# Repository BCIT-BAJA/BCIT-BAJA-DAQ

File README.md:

# Problem 
During the last BAJA competition,The BAJA team was unable to measure dynamic forces applied onto the suspension of the car. As a result, during the last competition, it bent.

The telemetry system for BCIT-BAJA car, collects strain across suspension components of car to allow BAJA to optimize material and reinforce weak areas of suspension.
As well as collect other data such as linear/angular acceleration.

There consists of 2 parts of this project. 

**PART B** the amplification of the (-15-15mV) analog strain signal to (0-3.0V) which is then routed to

**PART A**, which collects the 8 conditioned analog signals and is transmitted/received over a 915MHz antenna

# MAINBOARD( PART A)

Power supply circuitry

Conditioning of analog signals 

Additional peripherals used

# Amplifier circuit ( PART B) - 

Example of LTSPICE simulation used for amplifier board + signal conditioning

Verified amplifier board working

# Results of real-world appied force vs output voltage

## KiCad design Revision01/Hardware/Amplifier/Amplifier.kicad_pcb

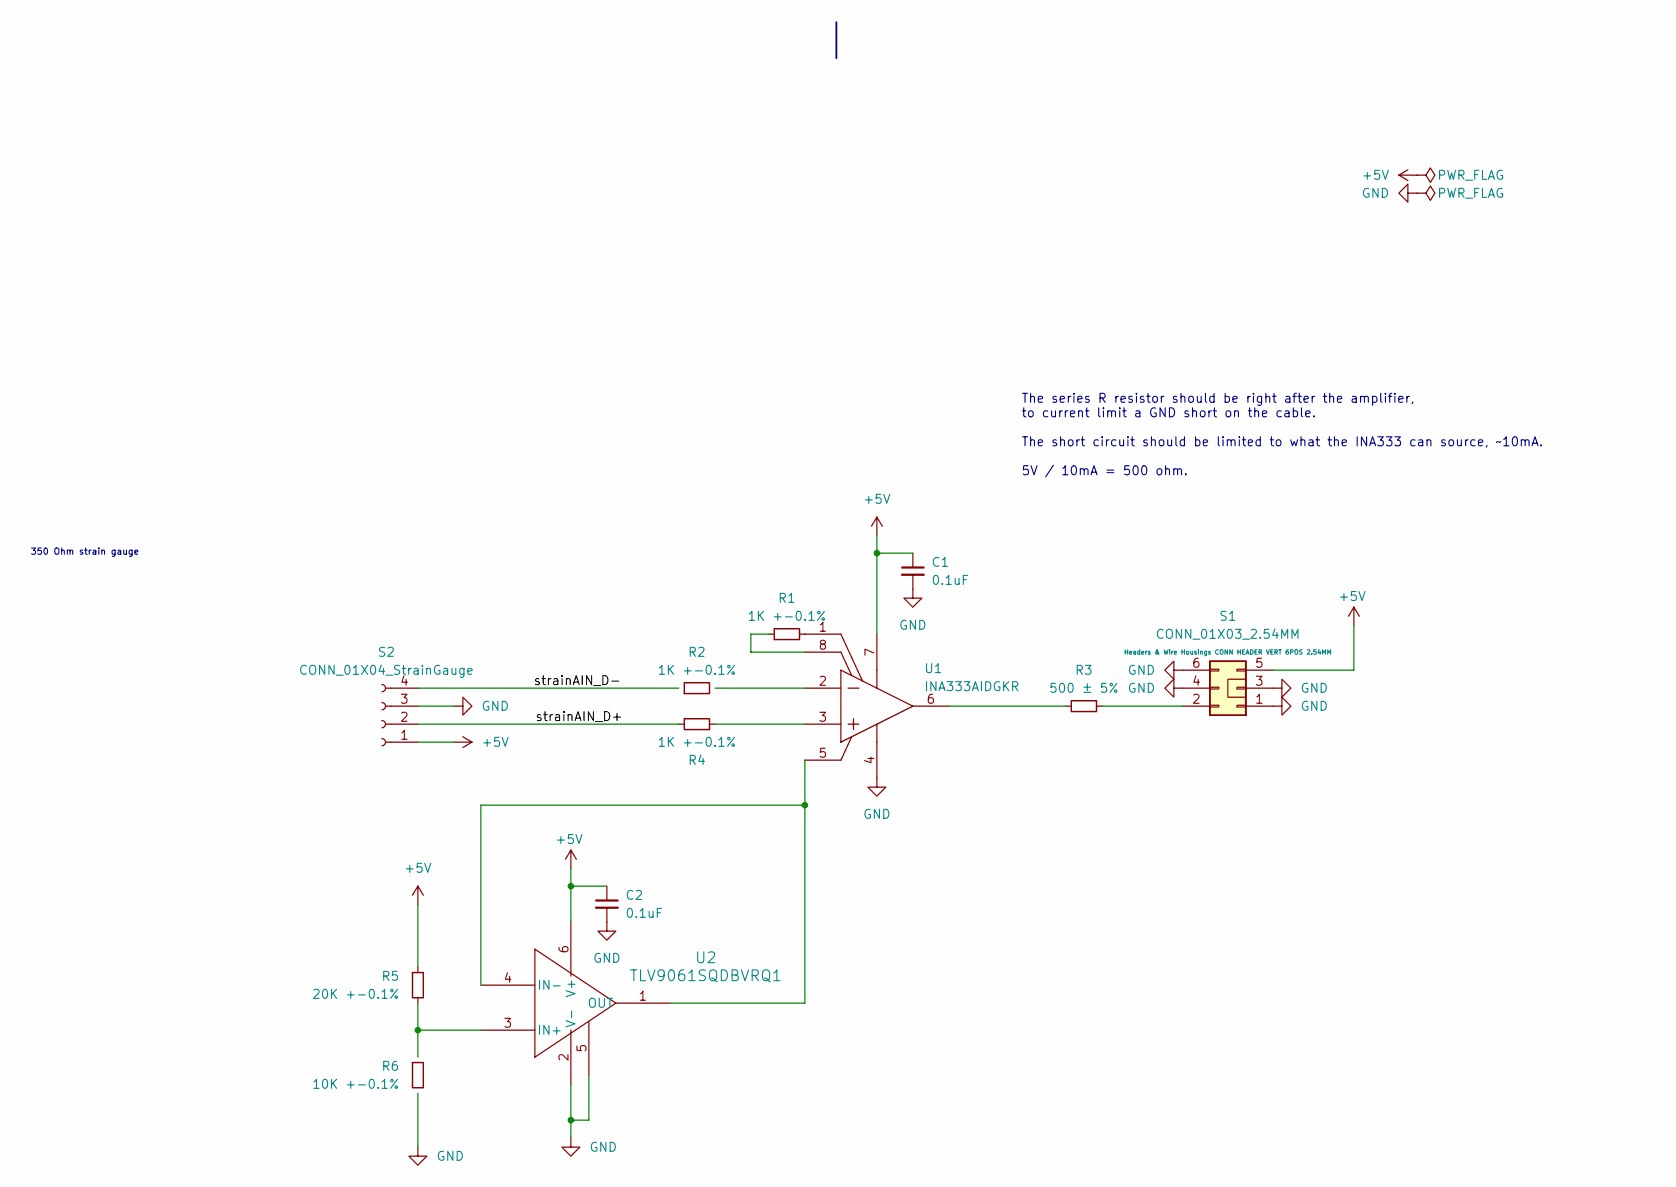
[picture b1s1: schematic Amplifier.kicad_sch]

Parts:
C1, C2: 0.1uF; C_0805_2012Metric_Pad1.18x1.45mm_HandSolder; Manufacturer Part Number CL21B104KBCNNWC; Mouser Part Number 187-CL21B104KBCNNWC
R1, R2, R4: 1K +-0.1%; R_0805_2012Metric_Pad1.20x1.40mm_HandSolder; Manufacturer Part Number MCU08050D1001BP500; Mouser Part Number 594-MCU0805D1001BP5
R3: 500 ± 5%; R_0805_2012Metric_Pad1.20x1.40mm_HandSolder; Manufacturer Part Number MCU0805MD4990DP500; Mouser Part Number 594-MCU0805MD4990DP5
R5: 20K +-0.1%; R_0805_2012Metric_Pad1.20x1.40mm_HandSolder; Manufacturer Part Number RG2012P-203-B-T5; Mouser Part Number 754-RG2012P-203-B-T5
R6: 10K +-0.1%; R_0805_2012Metric_Pad1.20x1.40mm_HandSolder; Manufacturer Part Number RG2012P-103-B-T5; Mouser Part Number 754-RG2012P-103-B-T5
S1: CONN_01X03_2.54MM; AdamTech_BHR-06-VUA; Manufacturer Part Number BHR-06-VUA; Mouser Part Number 737-BHR-06-VUA
S2: CONN_01X04_StrainGauge; CONN_01X04
U1: INA333AIDGKR; INA333AIDGKR_SOP65P490X110-8N; Manufacturer Part Number INA333AIDGKR; Mouser Part Number 595-INA333AIDGKR
U2: TLV9061SQDBVRQ1; TSOT-23-6; Manufacturer Part Number TLV9061SQDBVRQ1; Mouser Part Number 595-TLV9061SQDBVRQ1

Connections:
+5V: C1.1, C2.1, R5.1, S1.5, S2.1, U1.7 (V+), U2.6 (V+)
/strainAIN_D+: R4.2, S2.2
/strainAIN_D-: R2.1, S2.4
GND: C1.2, C2.2, R6.2, S1.1, S1.3, S1.4, S1.6, S2.3, U1.4 (V-), U2.2 (V-), U2.5
unnamed: R1.1, U1.8 (RG)
unnamed: R1.2, U1.1 (RG)
unnamed: R3.1, S1.2
unnamed: U1.5 (REF), U2.1 (OUT), U2.4 (IN-)
unnamed: R4.1, U1.3 (VIN+)
unnamed: R2.2, U1.2 (VIN-)
unnamed: R3.2, U1.6 (VOUT)
unnamed: R5.2, R6.1, U2.3 (IN+)

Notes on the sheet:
350 Ohm strain gauge
The series R resistor should be right after the amplifier, to current limit a GND short on the cable. The short circuit should be limited to what the INA333 can source, ~10mA. 5V / 10mA = 500 ohm.

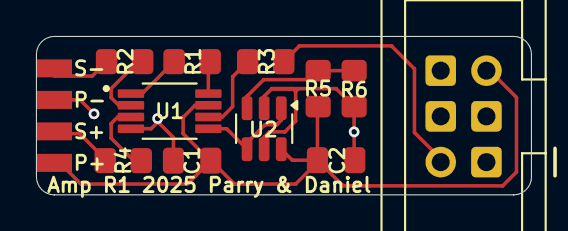
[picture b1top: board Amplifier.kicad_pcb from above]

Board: 2 copper layers, 27.5 x 8.8 mm, 12 parts (0 on the bottom side), 12 nets.

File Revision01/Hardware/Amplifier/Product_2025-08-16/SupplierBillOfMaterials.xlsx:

# | Reference | Quantity | Qty | Qty Multiplier | Value | Description | Package | Footprint | Detailed Description | Datasheet | Manufacturer | Manufacturer Part Number | Mouser Link | Mouser Part Number | Exclude from BOM | DNP | Exclude from Board
1 | C1,C2 | 2 | 2 |  | 0.1uF | Multilayer Ceramic Capacitors MLCC - SMD/SMT 100nF+/-10% 50V X7R 0805 | 0805 (2012 Metric) | Capacitor_SMD:C_0805_2012Metric_Pad1.18x1.45mm_HandSolder |  | https://www.mouser.ca/datasheet/2/585/MLCC-1837944.pdf | Samsung Electro-Mechanics | CL21B104KBCNNWC | https://www.mouser.ca/ProductDetail/Samsung-Electro-Mechanic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 | 187-CL21B104KBCNNWC
2 | R1,R2,R4 | 3 | 3 |  | 1K +-0.1% | Thin Film Resistors - SMD .05W 1Kohms 0.1% 0805 25ppm | 0805 (2012 Metric) | Resistor_SMD:R_0805_2012Metric_Pad1.20x1.40mm_HandSolder |  | https://www.vishay.com/doc?28700 | Vishay / Beyschlag | MCU08050D1001BP500 | https://www.mouser.ca/ProductDetail/Vishay-Beyschlag/MCU0805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 | 594-MCU0805D1001BP5
3 | R3 | 1 | 1 |  | 500 ± 5% | Thin Film Resistors - SMD .2W 499ohms .5% 0805 25ppm Auto | 0805 (2012 Metric) | Resistor_SMD:R_0805_2012Metric_Pad1.20x1.40mm_HandSolder |  | https://www.vishay.com/doc?28952 | Vishay / Beyschlag | MCU0805MD4990DP500 | https://www.mouser.ca/ProductDetail/Vishay-Beyschlag/MCU0805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 | 594-MCU0805MD4990DP5
4 | R5 | 1 | 1 |  | 20K +-0.1% | Thin Film Resistors - SMD 1/8W 20K Ohms 0.1% 0805 25ppm | 0805 (2012 Metric) | Resistor_SMD:R_0805_2012Metric_Pad1.20x1.40mm_HandSolder |  | https://www.mouser.ca/datasheet/2/392/n_catalog_partition01_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 | Susumu | RG2012P-203-B-T5 | https://www.mouser.ca/ProductDetail/Susumu/RG2012P-203-B-T5?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 | 754-RG2012P-203-B-T5
5 | R6 | 1 | 1 |  | 10K +-0.1% | Thin Film Resistors - SMD 1/8W 10K Ohms 0.1% 0805 25ppm | 0805 (2012 Metric) | Resistor_SMD:R_0805_2012Metric_Pad1.20x1.40mm_HandSolder |  | https://www.mouser.ca/datasheet/2/392/n_catalog_partition01_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 | Susumu | RG2012P-103-B-T5 | https://www.mouser.ca/ProductDetail/Susumu/RG2012P-103-B-T5?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 | 754-RG2012P-103-B-T5
6 | U2 | 1 | 1 |  | TLV9061SQDBVRQ1 | Operational Amplifiers - Op Amps Automotive single 5.5-V 10-MHz rail-to | SOT-23-6 | Package_TO_SOT_SMD:TSOT-23-6 |  | https://www.ti.com/lit/gpn/tlv9064-q1 | Texas Instruments | TLV9061SQDBVRQ1 | https://www.mouser.ca/ProductDetail/Texas-Instruments/TLV906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 | 595-TLV9061SQDBVRQ1
7 | U1 | 1 | 1 |  | INA333AIDGKR | Instrumentation Amplifiers Lo Pwr Prec Inst Amp A 595-INA333AIDGKT | VSSOP-8 | Lib:INA333AIDGKR_SOP65P490X110-8N |  | https://www.ti.com/lit/gpn/ina333 | Texas Instruments | INA333AIDGKR | https://www.mouser.ca/ProductDetail/Texas-Instruments/INA333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 | 595-INA333AIDGKR
35 | U4 | 2 | 1 | 2 | Adafruit 3070 | RFM69HCW TRANSCEIVER RADIO BREAK | Module | Lib:Adafruit3070 | RFM69HCW - Transceiver 868MHz, 915MHz Evaluation Board | https://cdn-learn.adafruit.com/downloads/pdf/adafruit-rfm69h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 | Adafruit Industries LLC | 3070 | https://www.mouser.ca/ProductDetail/Adafruit/3070?qs=AGnqjqv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 | 485-3070 | https://www.digikey.ca/en/products/detail/adafruit-industrie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 | 1528-1665-ND
 |  |  |  | NOTE: The Adafruit is unavailable on digikey at this time, so it is bundled wit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

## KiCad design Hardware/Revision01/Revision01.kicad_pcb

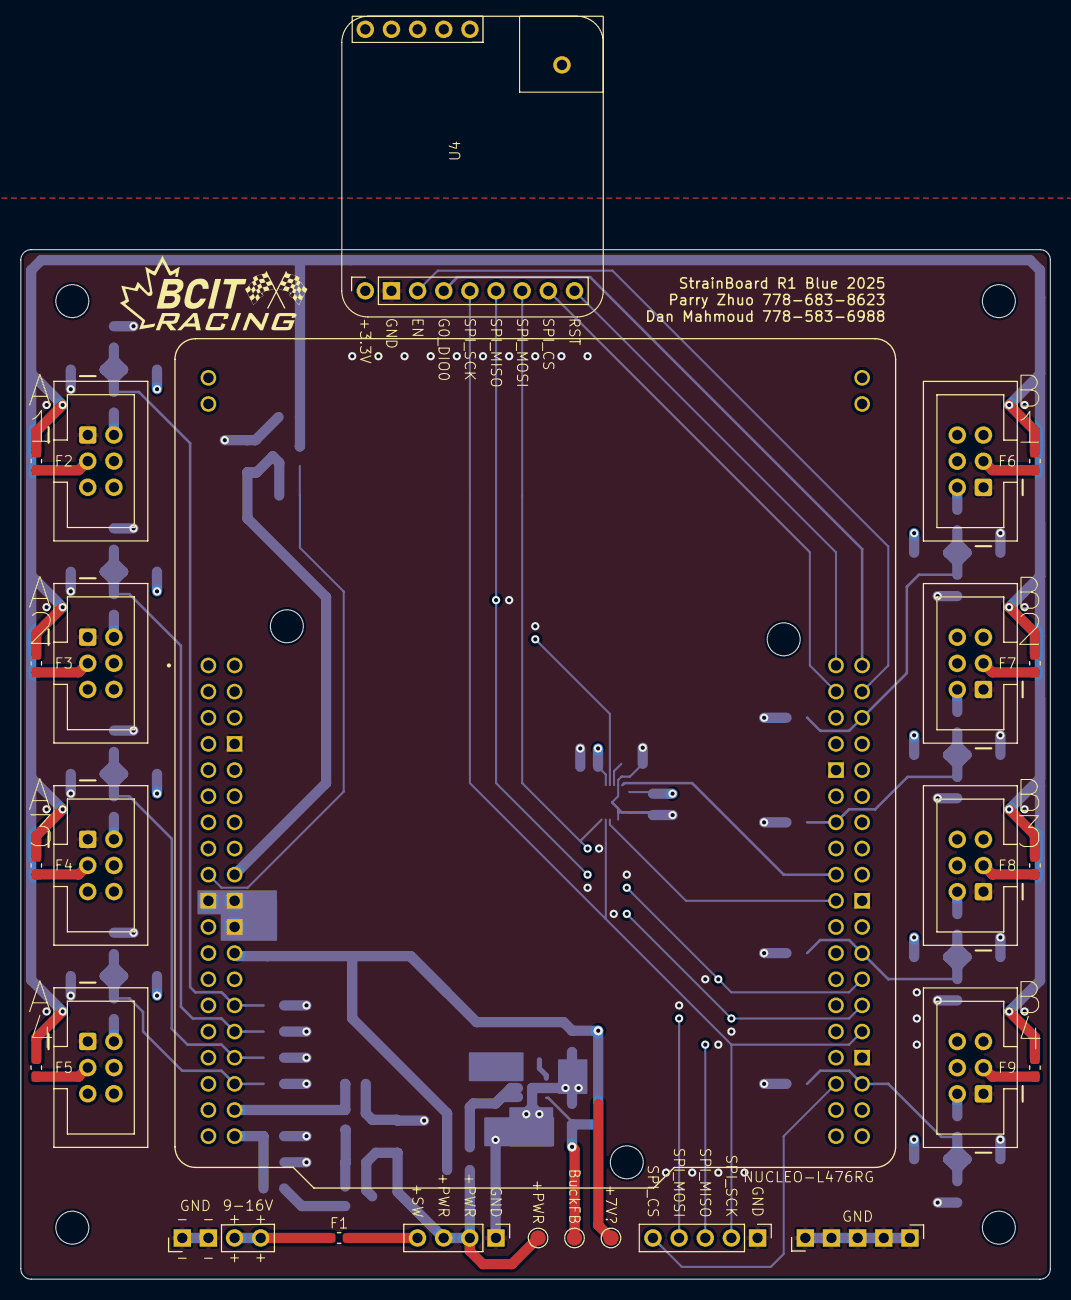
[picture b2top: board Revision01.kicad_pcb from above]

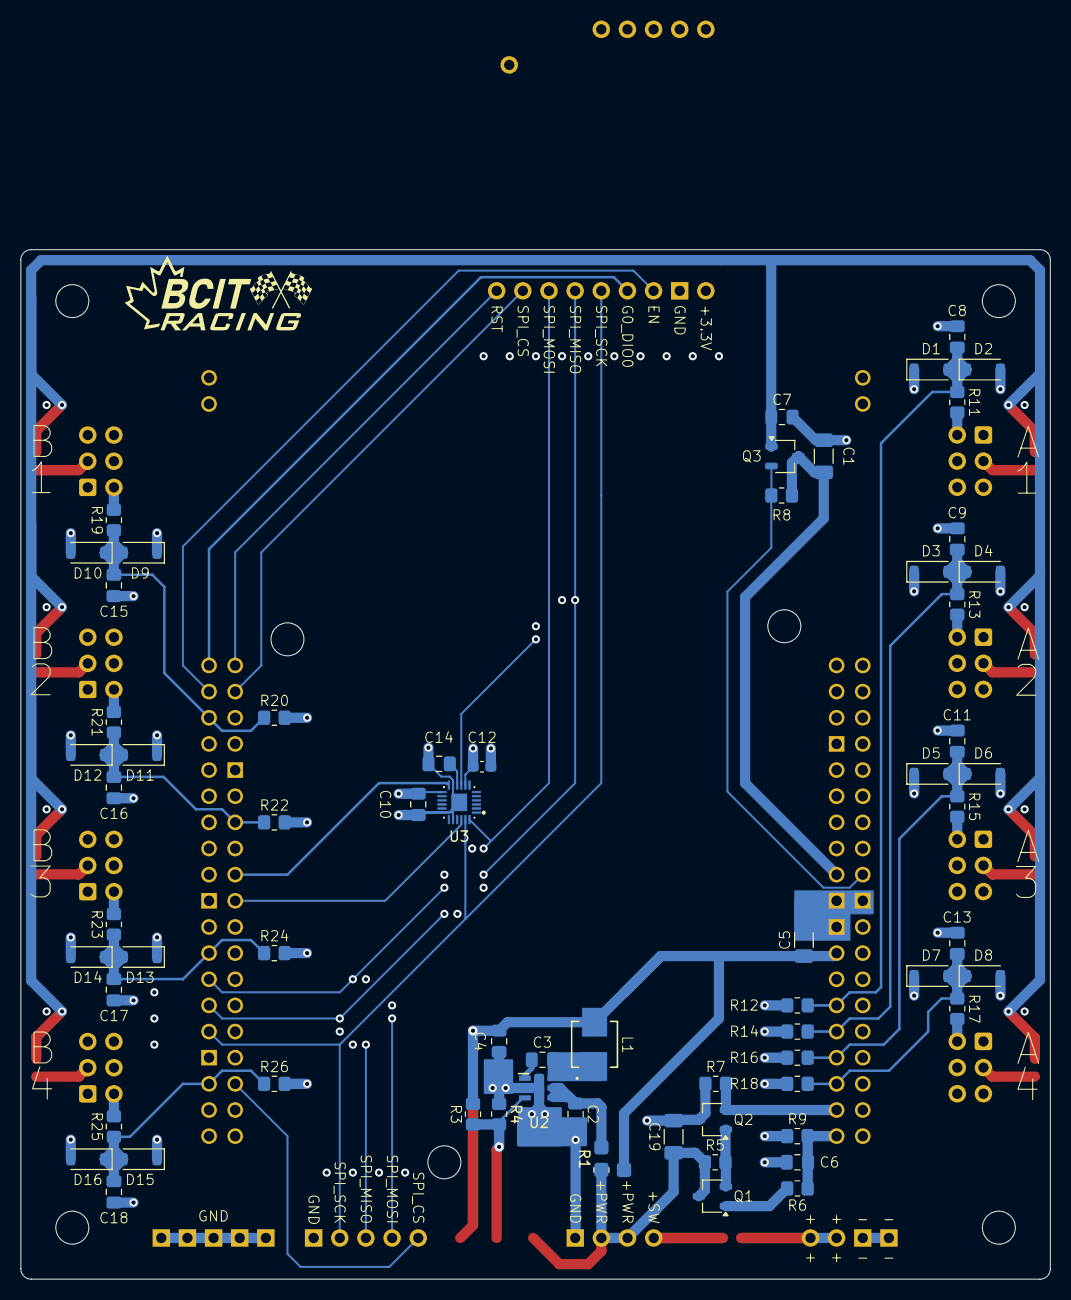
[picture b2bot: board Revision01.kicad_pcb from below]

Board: 4 copper layers, 100.0 x 100.0 mm, 95 parts (65 on the bottom side), 52 nets.

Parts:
C1, C19: 22uF ±10%; C_1206_3216Metric_Pad1.33x1.80mm_HandSolder
C2, C4: 1uF, X7R; C_0805_2012Metric_Pad1.18x1.45mm_HandSolder
C3: 0.1µF, X7R; C_0805_2012Metric_Pad1.18x1.45mm_HandSolder
C5: 10uF, X7R; C_1206_3216Metric_Pad1.33x1.80mm_HandSolder
C6, C7, C8, C9, C11, C13, C15, C16, C17, C18: 0.1uF ±10%; C_0805_2012Metric_Pad1.18x1.45mm_HandSolder
C10, C14: 0.1µF ±10%, Ceramic, X7R, >2V; C_0805_2012Metric_Pad1.18x1.45mm_HandSolder
C12: 10nF ±10%, Ceramic, X7R, >4V; C_0603_1608Metric_Pad1.08x0.95mm_HandSolder
D1, D2, D3, D4, D5, D6, D7, D8, D9, D10, D11, D12, D13, D14, D15, D16: D_Zener_Small; D_SOD-123
F1: FAST-BLOW 375mA 32V 0.45Ω; Fuse_0603_1608Metric_Pad1.05x0.95mm_HandSolder
F2, F3, F4, F5, F6, F7, F8, F9: 70mA 5s Fusing, 7.5 Ohms; Fuse_0603_1608Metric_Pad1.05x0.95mm_HandSolder
H1, H2, H3, H4: MountingHole; MountingHole_3.2mm_M3
J3: Conn_01x04; BatterySwitch_PinHeader_1x04_P2.54mm_Vertical
J4: Conn_01x05; SPIExtra_PinHeader_1x05_P2.54mm_Vertical
J5: Conn_01x05; GND_PinHeader_1x05_P2.54mm_Vertical
J6, J7, J8, J9, J10, J11, J12, J13: IDC 6Pin Male Header; AdamTech_BHR-06-VUA
J20: Conn_01x04; Battery_PinHeader_1x04_P2.54mm_Vertical
L1: 150uH; LQH44PH151MPRL_IND_LQH44PN_PR_MUR-M
Q1, Q3: PMOS; TSOT-23
Q2: NMOS; TSOT-23
R1: 0; ZeroOhmSwitch_R_0805_2012Metric_Pad1.20x1.40mm_HandSolder
R3: 76.8K+- 1%, ±100ppm/°C; R_0805_2012Metric_Pad1.20x1.40mm_HandSolder
R4: 10K +-1%, ±100ppm/°C; R_0805_2012Metric_Pad1.20x1.40mm_HandSolder
R5, R7, R8: 10K ±1%; R_0805_2012Metric_Pad1.20x1.40mm_HandSolder
R6: 15K ±1%; R_0805_2012Metric_Pad1.20x1.40mm_HandSolder
R9: 5K ±1%; R_0805_2012Metric_Pad1.20x1.40mm_HandSolder
R11, R13, R15, R17, R19, R21, R23, R25: 150 ±1%; R_0805_2012Metric_Pad1.20x1.40mm_HandSolder
R12, R14, R16, R18, R20, R22, R24, R26: 1M ±1%; R_0805_2012Metric_Pad1.20x1.40mm_HandSolder
TP1, TP2, TP4: TestPoint; TestPoint_Pad_D1.5mm
U1: NUCLEO-L476RG; MODULE_NUCLEO-L476RG
U2: LMR51603XFDBVR; LMR51603XFDBVR_DBV0006A-MFG-IPC_C
U3: MPU-6500; MPU-6500_QFN40P300X300X95-25N
U4: Adafruit 3070; Adafruit3070

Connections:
+3.3V: C10.1, C12.1, D1.1 (K), D3.1 (K), D5.1 (K), D7.1 (K), D9.1 (K), D11.1 (K), D13.1 (K), D15.1 (K), U1.CN7_5 (VDD), U1.CN7_16 (+3V3), U3.8 (VDDIO), U3.13 (VDD), U4.1 (VIN)
+5V: C1.1, Q3.3 (S), R8.2, U1.CN7_18 (+5V)
+VBattery: C19.1, J3.2, J3.3, Q1.3 (S), R1.1, R5.2, TP1.1
+VBattery_or_7V: C4.1, C5.1, L1.2, R1.3, R3.2, TP4.1, U1.CN7_24 (VIN)
/AIn_BatteryV: C6.1, R6.1, R9.2, U1.CN7_38 (PC0/ADC123_IN1/LPUART1_RX/LPTIM2_IN1)
/AIn_StrainV_1: C8.1, D1.2 (A), D2.1 (K), R11.1, R12.1, U1.CN7_28 (PA0/ADC12_IN5/USART2_CTS/UART4_TX/TIM2_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)
/AIn_StrainV_2: C9.1, D3.2 (A), D4.1 (K), R13.1, R14.1, U1.CN7_30 (PA1/ADC12_IN6/USART2_RTS_DE/UART4_RX/TI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)
/AIn_StrainV_3: C11.1, D5.2 (A), D6.1 (K), R15.1, R16.1, U1.CN7_32 (PA4/ADC12_IN9/DAC1_OUT1/SPI1_NSS/SPI3_N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)
/AIn_StrainV_4: C13.1, D7.2 (A), D8.1 (K), R17.1, R18.1, U1.CN7_34 (PB0/ADC12_IN15/USART3_CK)
/AIn_StrainV_5: C15.1, D9.2 (A), D10.1 (K), R19.1, R20.1, U1.CN10_6 (PC5/ADC12_IN14/USART3_RX)
/AIn_StrainV_6: C16.1, D11.2 (A), D12.1 (K), R21.1, R22.1, U1.CN10_13 (PA6/ADC12_IN11/SPI1_MISO/USART3_CTS/TIM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)
/AIn_StrainV_7: C17.1, D13.2 (A), D14.1 (K), R23.1, R24.1, U1.CN10_24 (PB1/ADC12_IN16/USART3_RTS_DE/LPTIM2_IN1)
/AIn_StrainV_8: C18.1, D15.2 (A), D16.1 (K), R25.1, R26.1, U1.CN10_34 (PC4/ADC12_IN13/USART3_TX)
/BuckFB: R3.1, R4.2, TP2.1, U2.3 (FB)
/BuckSW: C3.2, L1.1, U2.6 (SW)
/GPIO_ANT_Enable: U1.CN10_4 (PC6), U4.3 (EN)
/GPIO_ANT_Reset: U1.CN10_1 (PC9/TIM8_BKIN2_COMP1), U4.9 (RST)
/GPIO_ANT_SPI_CS: U1.CN10_3 (PB8/CAN1_RX/TIM16_CH1), U4.8 (CS)
/GPIO_BatteryV_Enable: Q2.2 (G), R7.2, U1.CN7_36 (PC1/ADC123_IN2/LPUART1_TX)
/GPIO_Extra_SPI_CS: J4.5, U1.CN10_33 (PA10/USART1_RX/TIM17_BKIN)
/GPInterruptPB6_MPU: U1.CN10_17 (PB6/USART1_TX/TIM16_CH1N), U3.12 (INT)
/GPInterruptPC8_ANT_DIO0: U1.CN10_2 (PC8), U4.4 (G0_DIO0)
/SPI2_MISO: J4.3, U1.CN10_28 (PB14/SPI2_MISO/USART3_RTS_DE/TIM15_CH1), U3.9 (AD0/SDO), U4.6 (MISO)
/SPI2_MOSI: J4.4, U1.CN10_26 (PB15/RTC_REFIN/SPI2_MOSI/TIM15_CH2), U3.24 (SDA/SDI), U4.7 (MOSI)
/SPI2_SCK: J4.2, U1.CN10_30 (PB13/SPI2_SCK/USART3_CTS/LPUART1_CTS/TI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), U3.23 (SCL/SCLK), U4.5 (SCK)
/~GPIO_MPU_SPI_CS: U1.CN10_19 (PC7), U3.22 (nCS)
/~GPIO_StrainV_Enable_5VTolerant: Q3.2 (G), R8.1, U1.CN7_17 (PA15/JTDI/SPI1_NSS/SPI3_NSS/UART4_RTS_DE)
GND: C1.2, C2.2, C4.2, C5.2, C6.2, C7.2, C8.2, C9.2, C10.2, C11.2, C12.2, C13.2, C14.1, C15.2, C16.2, C17.2, C18.2, C19.2, D2.2 (A), D4.2 (A), D6.2 (A), D8.2 (A), D10.2 (A), D12.2 (A), D14.2 (A), D16.2 (A), J3.1, J4.1, J5.1, J5.2, J5.3, J5.4, J5.5, J6.1, J7.1, J8.1, J9.1, J10.1, J11.1, J12.1, J13.1, J20.1, J20.2, Q2.3 (S), R4.1, R7.1, R9.1, R12.2, R14.2, R16.2, R18.2, R20.2, R22.2, R24.2, R26.2, U1.CN7_8 (GND_CN7_8), U1.CN7_19 (GND_CN7_19), U1.CN7_20 (GND_CN7_20), U1.CN7_22 (GND_CN7_22), U1.CN10_9 (GND_CN10_9), U1.CN10_20 (GND_CN10_20), U1.CN10_32 (AGND), U2.2 (GND), U3.11 (FSYNC_or_GND), U3.18 (GND), U3.20 (RESV_GND), U3.25 (ThermalPad_typically_GND), U4.2 (GND)
unnamed: F1.2, J3.4
unnamed: J6.2, R11.2
unnamed: F2.2, J6.3
unnamed: J7.2, R13.2
unnamed: F3.2, J7.3
unnamed: J8.2, R15.2
unnamed: F4.2, J8.3
unnamed: J9.2, R17.2
unnamed: F5.2, J9.3
unnamed: J10.2, R19.2
unnamed: F6.2, J10.3
unnamed: J11.2, R21.2
unnamed: F7.2, J11.3
unnamed: J12.2, R23.2
unnamed: F8.2, J12.3
unnamed: J13.2, R25.2
unnamed: F9.2, J13.3
unnamed: F1.1, J20.3, J20.4
unnamed: Q1.1 (D), R6.2
unnamed: Q1.2 (G), Q2.1 (D), R5.1
unnamed: C7.1, F2.1, F3.1, F4.1, F5.1, F6.1, F7.1, F8.1, F9.1, Q3.1 (D)
unnamed: C3.1, U2.1 (CB)
unnamed: C2.1, R1.2, U2.4 (EN), U2.5 (VIN)
unnamed: C14.2, U3.10 (REGOUT)

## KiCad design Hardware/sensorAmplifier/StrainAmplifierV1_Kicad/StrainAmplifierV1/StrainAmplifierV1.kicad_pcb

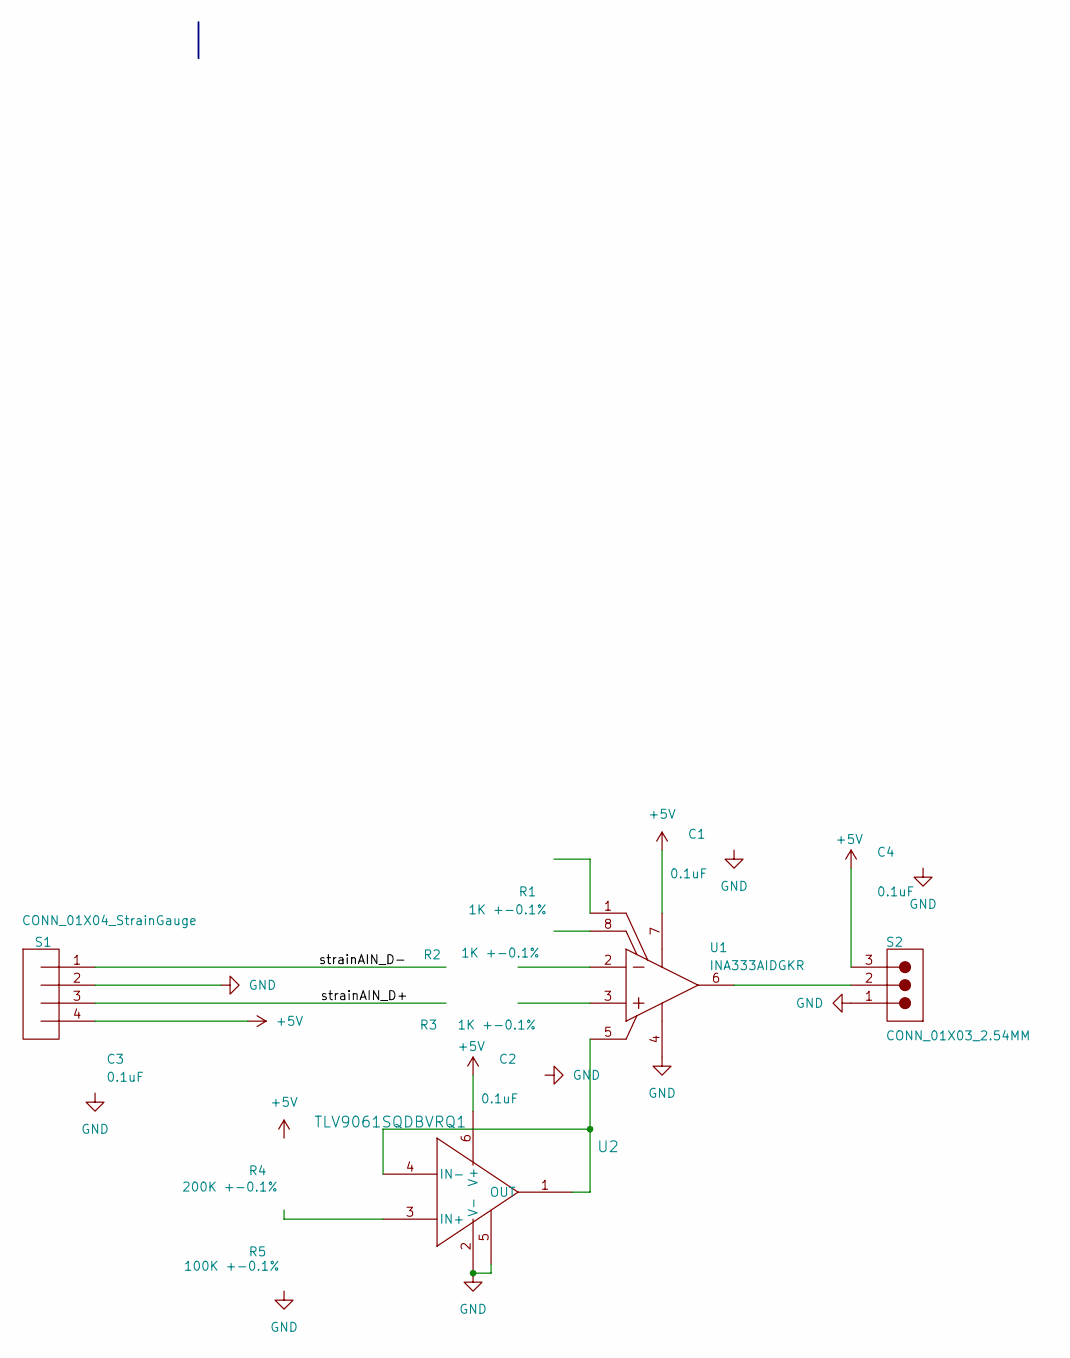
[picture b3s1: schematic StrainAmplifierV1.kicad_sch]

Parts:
C1, C2, C3, C4: 0.1uF; C_0805_2012Metric_Pad1.18x1.45mm_HandSolder; VOLTAGE RATING 50; MANUFACTURER PART NUMBER CC0805JRNPO9BN250
R1, R2, R3: 1K +-0.1%; R_0805_2012Metric_Pad1.20x1.40mm_HandSolder; MANUFACTURER PART NUMBER RNCS0805BKE1K00
R4: 200K +-0.1%; R_0805_2012Metric_Pad1.20x1.40mm_HandSolder; MANUFACTURER PART NUMBER RN73R2ATTD2003B25
R5: 100K +-0.1%; R_0805_2012Metric_Pad1.20x1.40mm_HandSolder; MANUFACTURER PART NUMBER RNCS0805BKE100K
S1: CONN_01X04_StrainGauge; CONN_01X04
S2: CONN_01X03_2.54MM; PinHeader_1x03_P2.54mm_Vertical
U1: INA333AIDGKR; VSSOP-8_3x3mm_P0.65mm; PARTNUMBER INA333AIDGKR
U2: TLV9061SQDBVRQ1; TSOT-23-6

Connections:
+5V: C1.1, C2.1, C3.2, C4.2, R4.2, S1.4, S2.3, U1.7 (V+), U2.6 (V+)
/strainAIN_D+: R3.2, S1.3
/strainAIN_D-: R2.2, S1.1
GND: C1.2, C2.2, C3.1, C4.1, R5.1, S1.2, S2.1, U1.4 (V-), U2.2 (V-), U2.5
unnamed: R1.1, U1.8 (RG)
unnamed: R1.2, U1.1 (RG)
unnamed: U1.5 (REF), U2.1 (OUT), U2.4 (IN-)
unnamed: R3.1, U1.3 (VIN+)
unnamed: R2.1, U1.2 (VIN-)
unnamed: S2.2, U1.6 (VOUT)
unnamed: R4.1, R5.2, U2.3 (IN+)

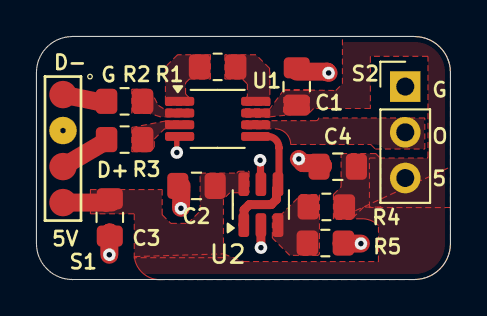
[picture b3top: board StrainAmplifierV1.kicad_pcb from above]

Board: 2 copper layers, 23.0 x 13.5 mm, 13 parts (0 on the bottom side), 11 nets.

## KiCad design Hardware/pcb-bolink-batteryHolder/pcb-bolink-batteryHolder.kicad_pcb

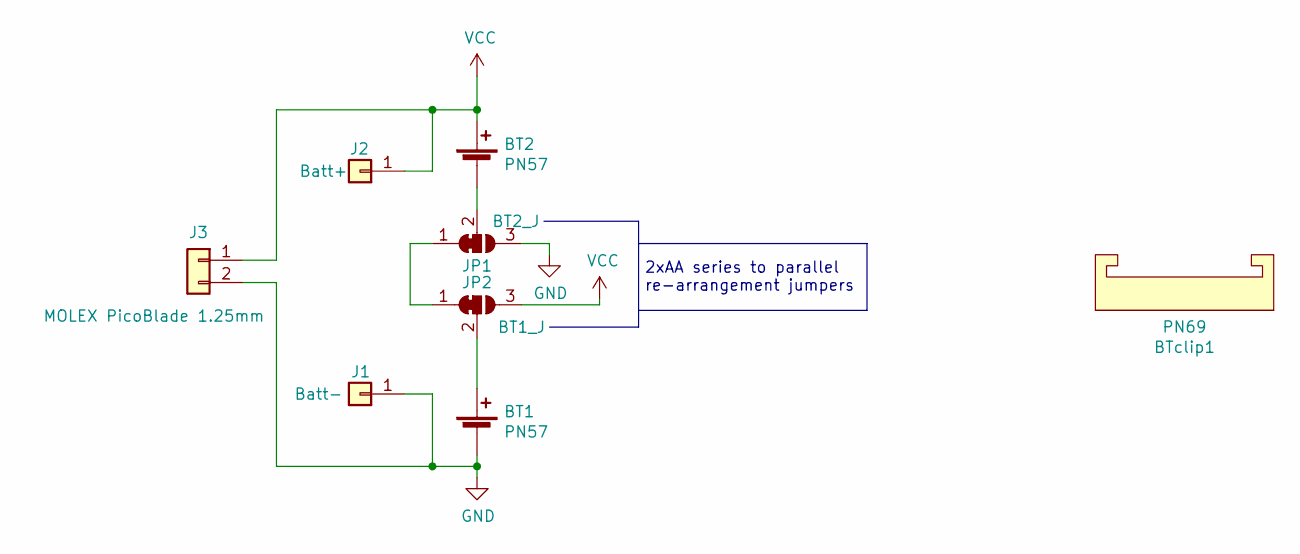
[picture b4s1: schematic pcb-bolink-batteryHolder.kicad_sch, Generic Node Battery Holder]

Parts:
BT1, BT2: PN57; keystone-PN57; MPN 57
BTclip1: PN69; Keystone_69_clip; MPN 69
J1: Batt-; TestPoint_Keystone_5019_Minature; MPN DNM
J2: Batt+; TestPoint_Keystone_5019_Minature; MPN DNM
J3: MOLEX PicoBlade 1.25mm; Molex_PicoBlade_53398-0271_1x02-1MP_P1.25mm_Vertical; MPN 0533980271
JP1: BT2_J; SolderJumper-3_P1.3mm_Bridged2Bar12_Pad1.0x1.5mm_NumberLabe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
JP2: BT1_J; SolderJumper-3_P1.3mm_Bridged2Bar12_Pad1.0x1.5mm_NumberLabe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

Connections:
GND: BT1.2 (-), J1.1, J3.2, JP1.3 (B)
unnamed: BT1.1 (+), JP2.2 (C)
unnamed: BT2.2 (-), JP1.2 (C)
unnamed: JP1.1 (A), JP2.1 (A)
VCC: BT2.1 (+), J2.1, J3.1, JP2.3 (B)

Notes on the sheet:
2xAA series to parallel re-arrangement jumpers

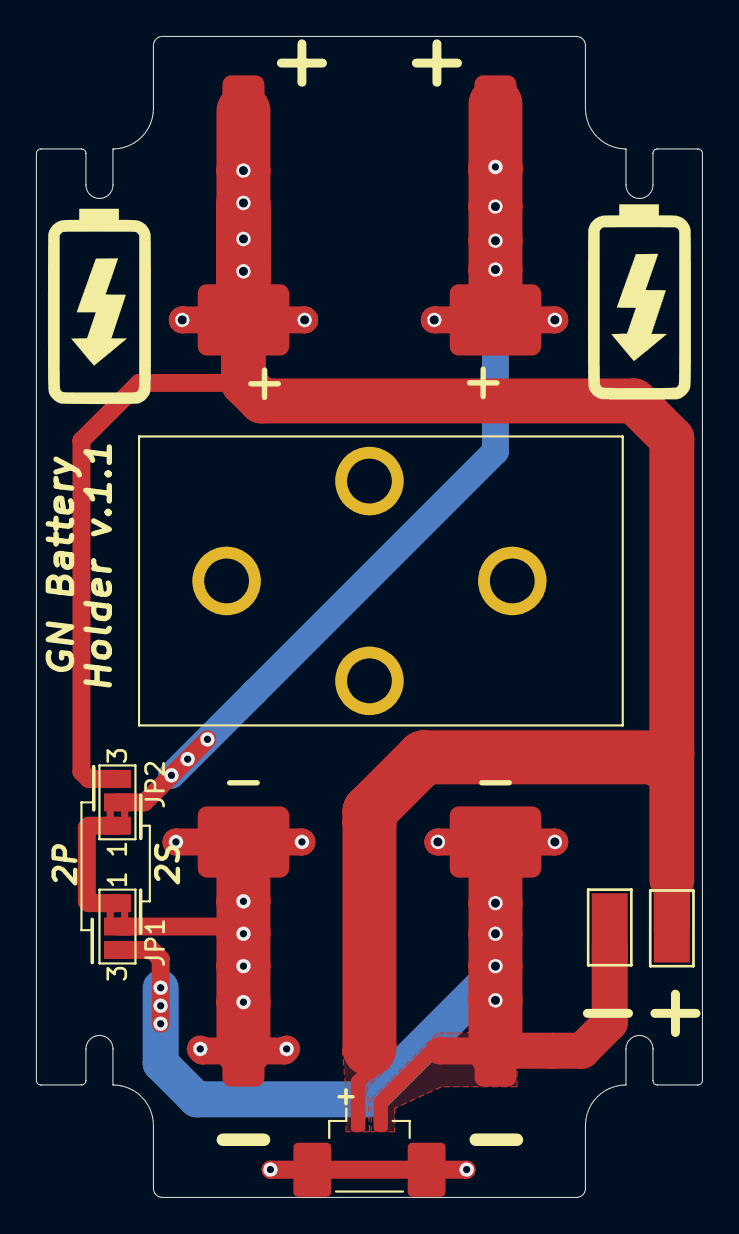
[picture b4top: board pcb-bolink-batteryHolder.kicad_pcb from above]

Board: 2 copper layers, 37.0 x 64.5 mm, 10 parts (0 on the bottom side), 5 nets.

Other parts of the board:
G-BT1, G-BT1#2: LOGO; Icon_Battery_1200px

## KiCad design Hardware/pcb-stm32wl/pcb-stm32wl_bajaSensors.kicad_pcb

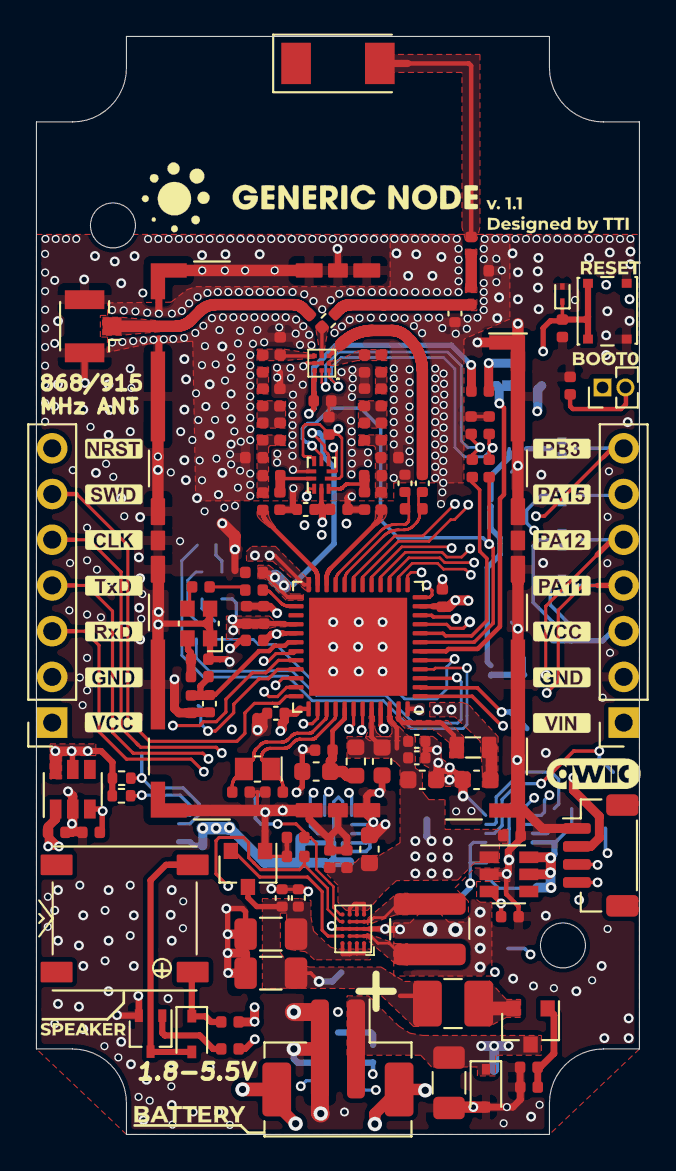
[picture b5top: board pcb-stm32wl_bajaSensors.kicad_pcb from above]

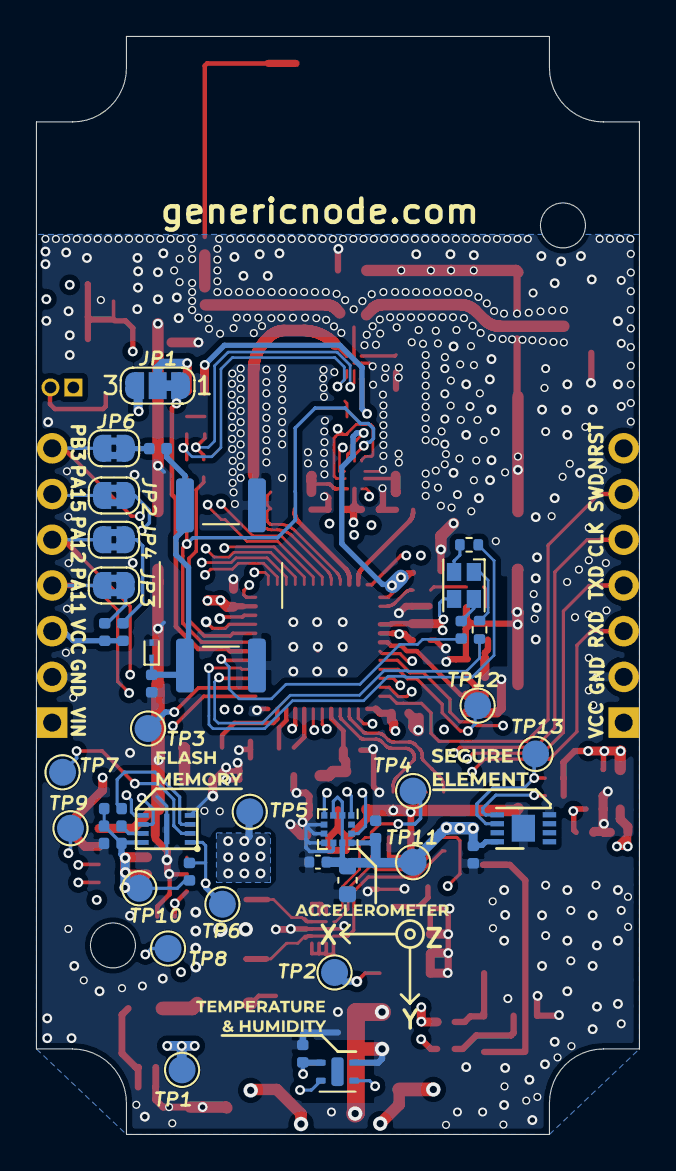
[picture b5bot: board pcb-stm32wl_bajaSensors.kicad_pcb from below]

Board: 4 copper layers, 33.5 x 61.0 mm, 182 parts (45 on the bottom side), 87 nets.

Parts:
AE1: NN02-201; Antenna_Fractus_NN02-201
C1, C4, C5: 100uF; C_1206_3216Metric
C2, C55: DNM; C_0402_1005Metric
C3, C6, C8, C11: 1uF; C_0402_1005Metric
C7, C9, C10, C14, C16, C17, C18, C20, C24, C29, C57, C59, C60, C61, C62, C63, C64, C65: 100nF; C_0402_1005Metric
C12: 22uF; C_0603_1608Metric
C13, C15, C27: 4.7uF; C_0603_1608Metric
C19, C21, C22, C32, C33, C41, C42: 33pF; C_0402_1005Metric
C23: 47pF; C_0402_1005Metric
C25: 47nF; C_0402_1005Metric
C26: 68pF; C_0402_1005Metric
C28: 470nF; C_0603_1608Metric
C30, C37, C44: 2.7pF; C_0402_1005Metric
C31: 3.6pF; C_0402_1005Metric
C34: 10nF; C_0402_1005Metric
C35, C46, C49: 5.6pF; C_0402_1005Metric
C36: 6.8pF; C_0402_1005Metric
C38: 2.4pF; C_0402_1005Metric
C39: 3.3pF; C_0402_1005Metric
C40: 3.9pF; C_0402_1005Metric
C43, C47, C48, C50: 1nF; C_0402_1005Metric
C45: 1.3pF; C_0402_1005Metric
C58: 10uF; C_0603_1608Metric
D1: PESD5V0S1BA; D_SOD-323
D2: 1N4148WSF-7; D_SOD-323F_custom
D3: FM-B2020RGBA; LED_Cree-PLCC4_2x2mm_CW
D4, D5: ESD9D5V; D_SOD-923
F1: PTC 13V 1A; Fuse_1210_3225Metric_Castellated
FB1: 600R @100MHz; L_0603_1608Metric
G-ACCELL: LOGO; LAbel_ACCELL_2000px
G-BAT: LOGO; Label_BATTERY_2500px
G-BOOT0: LOGO; Label_BOOT0_4000px
G-CLK: LOGO; PinName_CLK
G-FLASH: LOGO; Label_FLASH_3000px
G-GND, G-GND2: LOGO; PinName_GND
G-GNSE: LOGO; Logo_GN_new_2000px
G-NRST: LOGO; PinName_NRST
G-PA11: LOGO; PinName_PA11
G-PA12: LOGO; PinName_PA12
G-PA15: LOGO; PinName_PA15
G-PB3: LOGO; PinName_PB3
G-QWIIC: LOGO; Logo_qwiic_4000px
G-RST: LOGO; Label_RESET_4000px
G-RXD: LOGO; PinName_RxD
G-SE: LOGO; Label_SE_3000px
G-SPKR: LOGO; Label_Speaker
G-SWD: LOGO; PinName_SWD
G-TH: LOGO; Label_T_H_2000px
G-TXD: LOGO; PinName_TxD
G-VCC, G-VCC2: LOGO; PinName_VCC
G-VIN: LOGO; PinName_VIN
G-version: LOGO; Logo_design_version_2000px
H1, H2: MountingHole; MountingHole_2.5mm
J1, J3, J5, J6: S1001-46R; RF_Shield_Clip_S1001-46R
J2: JST-PH; JST_PH_B2B-PH-SM4-TB_1x02-1MP_P2.00mm_Vertical
J4: RF_Shield_One_Piece; RF_Shield_SnapOn_30x20mm_w_Cutout_n_GND_Pads
J7: U.FL/iPEX; U.FL_Hirose_U.FL-R-SMT-1_Vertical
J8: DEBUG; PinSocket_1x07_P2.54mm_Vertical
J9: UART/I2C; PinSocket_1x07_P2.54mm_Vertical
J10: Qwiic; JST_SH_BM04B-SRSS-TB_1x04-1MP_P1.00mm_Vertical
JP1: VDD_RF_SW; SolderJumper-3_P1.3mm_Bridged12_RoundedPad1.0x1.5mm_NumberL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
JP2: BUZZ_KILL; SolderJumper-2_P1.3mm_Bridged2Bar_RoundedPad1.0x1.5mm
JP3: SDA2_CUT; SolderJumper-2_P1.3mm_Bridged2Bar_RoundedPad1.0x1.5mm
JP4: SCL2_CUT; SolderJumper-2_P1.3mm_Bridged2Bar_RoundedPad1.0x1.5mm
JP5: BOOT0; PinHeader_1x02_P1.27mm_Vertical
JP6: BTN_CUT; SolderJumper-2_P1.3mm_Bridged2Bar_RoundedPad1.0x1.5mm
L1: 2.2uH; L_HPC4012TF-2R2M
L2, L9: 3.3nH; L_0402_1005Metric
L3: 3.6nH; L_0402_1005Metric
L4: 15uH; L_0805_2012Metric_custom
L5: 11nH; L_0402_1005Metric
L6, L7: 47nH; L_0402_1005Metric
L8: 3nH; L_0402_1005Metric
L10: 1400R @1GHz; L_0402_1005Metric
L11: 6.8nH; L_0402_1005Metric
L12: 8.7nH; L_0402_1005Metric
L13: 27nH; L_0402_1005Metric
L14: 6.5nH; L_0402_1005Metric
L15: 8nH; L_0402_1005Metric
N1: BoLink-16174563; BoLink_704025
PZ1: MLT-7525; Buzzer_MLT-7525
Q1: PMV32UP,215; SOT-23
Q2: PMST4401,115; SOT-323_SC-70
R1, R9: 0R; R_0402_1005Metric
R2, R3, R4: 100K; R_0402_1005Metric
R5: 220R; L_0402_1005Metric
R6, R7, R8, R24: 100R; R_0402_1005Metric
R10, R11, R12: DNM; R_0402_1005Metric
R13: 10K; R_0402_1005Metric
R14, R15, R17, R18: 4K7; R_0402_1005Metric
R16, R21: 1K; R_0402_1005Metric
R19: 33R; R_0402_1005Metric
R20: 10K; L_0402_1005Metric
R22, R23: 330R; R_0402_1005Metric
SW1: USR_BTN; PushButton_KSC721GLFS
SW2: RESET; SW_SPST_SKSHABE010
TP1: VIN; TestPoint_Pad_D1.5mm
TP2: VBAT; TestPoint_Pad_D1.5mm
TP3: VBAT_READ_EN; TestPoint_Pad_D1.5mm
TP4: VBAT_ADC; TestPoint_Pad_D1.5mm
TP5: VCC; TestPoint_Pad_D1.5mm
TP6: CS; TestPoint_Pad_D1.5mm
TP7: MISO; TestPoint_Pad_D1.5mm
TP8: SCK; TestPoint_Pad_D1.5mm
TP9: MOSI; TestPoint_Pad_D1.5mm
TP10: VCC_F; TestPoint_Pad_D1.5mm
TP11: VCC_S; TestPoint_Pad_D1.5mm
TP12: SDA; TestPoint_Pad_D1.5mm
TP13: SCL; TestPoint_Pad_D1.5mm
U1, U3: TPS22917DBV; SOT-23-6
U2: TPS3839G18DBZT‎; SOT-23
U4: RP605Z283B; WLCSP-20-P3_1.994x1.609mm_Layout5x4_P0.4mm
U5: STM32WL55CCU6; QFN-48-1EP_7x7mm_P0.5mm_EP5.45x5.45mm
U6: TS3A5223RSWR; UQFN-10_1.4x1.8mm_P0.4mm
U7: BGS13S4N9; RFSW_BGS13S4N9E6327XTSA1
U8: MX25R1635; FLASH_UFDFN-8-MX25R1635F
U9: LIS2DH12; LGA-12_2x2mm_P0.5mm
U10: SHTC3; Sensirion_DFN-4-1EP_2x2mm_P1mm_EP0.7x1.6mm
U11: ATECC608B-TNGLORAU; DFN-8-1EP_3x2mm_P0.5mm_EP1.3x1.5mm
X1: 32MHz; Crystal_SMD_Abracon_ABM10-4Pin_2.5x2.0mm
Y1: 32.768KHz; Crystal_SMD_NX2012SA_32.768KHz

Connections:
+BATT: C4.2, C5.2, C6.1, C7.1, F1.1, TP2.1, U2.3, U4.A1, U4.B1, U4.C1, U4.D1
/LoRa MCU/BOOT0: JP5.2, R20.2, U5.19
/LoRa MCU/NRST: C65.2, D5.1, J8.7, SW2.2, U5.18
/LoRa MCU/PA2_TxD2: J8.4, U5.9
/LoRa MCU/PA3_RxD2: J8.3, U5.10
/LoRa MCU/PA5_SCK1: TP8.1, U5.13, U8.6
/LoRa MCU/PA8: U5.16, U9.11
/LoRa MCU/PA09_SCL1: R14.1, TP13.1, U5.17, U9.1, U10.2, U11.6
/LoRa MCU/PA10_SDA1: R17.2, TP12.1, U5.33, U9.4, U10.3, U11.5
/LoRa MCU/PA11_SDA2: J9.4, J10.3, JP3.2, U5.34
/LoRa MCU/PA12_SCL2: J9.5, J10.4, JP4.2, U5.35
/LoRa MCU/PA15: J9.6, JP2.1, U5.43
/LoRa MCU/PB2: C9.1, TP4.1, U4.D5, U5.31
/LoRa MCU/PB3: J9.7, JP6.1, U5.1
/LoRa MCU/PB4: R3.2, TP3.1, U4.D4, U5.2
/LoRa MCU/PB5: R21.1, U5.3
/LoRa MCU/PB6: R22.1, U5.4
/LoRa MCU/PB7: R23.1, U5.5
/LoRa MCU/RFI_N: C30.2, L5.1, U5.21
/LoRa MCU/RFI_P: C31.1, L5.2, U5.20
/LoRa MCU/SWCLK: J8.5, U5.42
/LoRa MCU/SWDIO: J8.6, U5.36
/Peripherals/FlashCS: R13.2, TP6.1, U5.12, U8.1
/Peripherals/MISO: TP7.1, U5.14, U8.2
/Peripherals/MOSI: TP9.1, U5.15, U8.5
/Peripherals/VCC_FLASH: C60.2, R11.1, R12.1, R13.1, TP10.1, U3.5, U3.6, U8.8
/Peripherals/VCC_SENSORS: C58.2, C59.2, C61.2, C62.2, C63.2, R14.2, R17.1, TP11.1, U1.5, U1.6, U9.2, U9.3, U9.9, U9.10, U10.1, U11.8
/Power Supply/LS1_SENSORS_EN: R2.2, U1.3, U5.32
/Power Supply/LS2_FLASH_EN: R4.2, U3.3, U5.38
FE_CTRL1: R7.2, U5.7, U6.4, U6.8
FE_CTRL2: R6.2, U5.8
FE_CTRL3: JP1.1, U5.6
GND: C1.1, C2.2, C3.2, C4.1, C5.1, C6.2, C7.2, C8.2, C9.2, C10.1, C11.2, C12.1, C13.2, C14.2, C15.2, C16.2, C17.2, C18.2, C19.2, C20.2, C21.2, C22.2, C23.2, C24.2, C25.1, C26.2, C27.2, C28.2, C29.2, C30.1, C32.1, C33.2, C34.1, C35.1, C36.1, C39.1, C40.1, C44.1, C45.1, C46.1, C47.1, C48.1, C49.1, C50.1, C55.1, C57.2, C58.1, C59.1, C60.1, C61.1, C62.1, C63.1, C64.1, C65.1, D1.2, D4.2, D5.2, J1.1, J2.2, J3.1, J4.1, J5.1, J6.1, J7.2, J8.2, J9.2, J10.1, L14.1, Q2.2, R1.1, R2.1, R3.1, R4.1, R20.1, SW1.2, SW2.1, U1.2, U2.1, U3.2, U4.A3, U4.B3, U4.C3, U4.D3, U5.48, U5.49, U6.6, U7.6, U7.9, U8.4, U8.9, U9.5, U9.6, U9.7, U9.8, U10.4, U11.4, U11.9, X1.1, X1.2
unnamed: AE1.2, L13.2
unnamed: C2.1, Q1.1, R1.2
unnamed: C25.2, C26.1, U5.24, U6.9
unnamed: C31.2, U7.3
unnamed: C32.2, L6.1, U6.7
unnamed: C33.1, L7.1, U6.10
unnamed: C34.2, L10.2, X1.4
unnamed: C35.2, C37.1, L2.2, L7.2, L8.1
unnamed: C36.2, C38.1, L3.2, L6.2, L9.1
unnamed: C37.2, C39.2, C42.1, L8.2
unnamed: C38.2, C40.2, C41.1, L9.2
unnamed: C41.2, L11.1
unnamed: C42.2, L12.1
unnamed: C43.1, R5.1
unnamed: C44.2, L11.2, U7.5
unnamed: C45.2, L12.2, U7.2
unnamed: C47.2, R6.1, U7.8
unnamed: C48.2, R7.1, U7.1
unnamed: C50.2, R8.2, U7.7
unnamed: C55.2, L15.1, R9.1
unnamed: C64.2, D4.1, R24.2, SW1.1
unnamed: D2.1, PZ1.1, R19.2
unnamed: D2.2, PZ1.2, Q2.3
unnamed: D3.1, R21.2
unnamed: D3.2, R23.2
unnamed: D3.4, R22.2
unnamed: F1.2, Q1.2
unnamed: J7.1, R10.1
unnamed: JP1.2, R8.1
unnamed: JP2.2, R16.1
unnamed: JP3.1, R15.1
unnamed: JP4.1, R18.2
unnamed: JP6.2, R24.1
unnamed: L1.1, U4.A4, U4.B4, U4.C4
unnamed: L1.2, U4.A2, U4.B2, U4.C2
unnamed: L2.1, U5.22
unnamed: L3.1, U5.23
unnamed: L13.1, L14.2, L15.2
unnamed: Q2.1, R16.2
unnamed: R5.2, X1.3
unnamed: R9.2, R10.2, U7.4
unnamed: R11.2, U8.7
unnamed: R12.2, U8.3
unnamed: U2.2, U4.D2
OSC32_IN: C46.2, U5.39, Y1.2
OSC32_OUT: C49.2, U5.40, Y1.1
OSC_IN: C43.2, U5.26
PB0_VDD_TCXO: C23.1, C24.1, L10.1, U5.30
VDDA: C15.1, C17.1, FB1.1, U5.41
VDDPA: C21.1, U5.25, U6.3
VDDRF: C3.1, C8.1, C10.2, C11.1, C12.2, C13.1, C14.1, C16.1, C18.1, C19.1, C20.1, C27.1, C29.1, C57.1, D3.3, FB1.2, J8.1, J9.3, J10.2, JP1.3, JP5.1, R15.2, R18.1, R19.1, TP5.1, U1.1, U3.1, U4.A5, U4.B5, U4.C5, U5.11, U5.28, U5.37, U5.44, U5.46, U6.1, U6.5
VDDRF1V55: C22.1, C28.1, L4.2, U5.29, U5.45, U6.2
VLXSMPS: L4.1, U5.47
Vin: C1.2, D1.1, J2.1, J9.1, Q1.3, TP1.1
